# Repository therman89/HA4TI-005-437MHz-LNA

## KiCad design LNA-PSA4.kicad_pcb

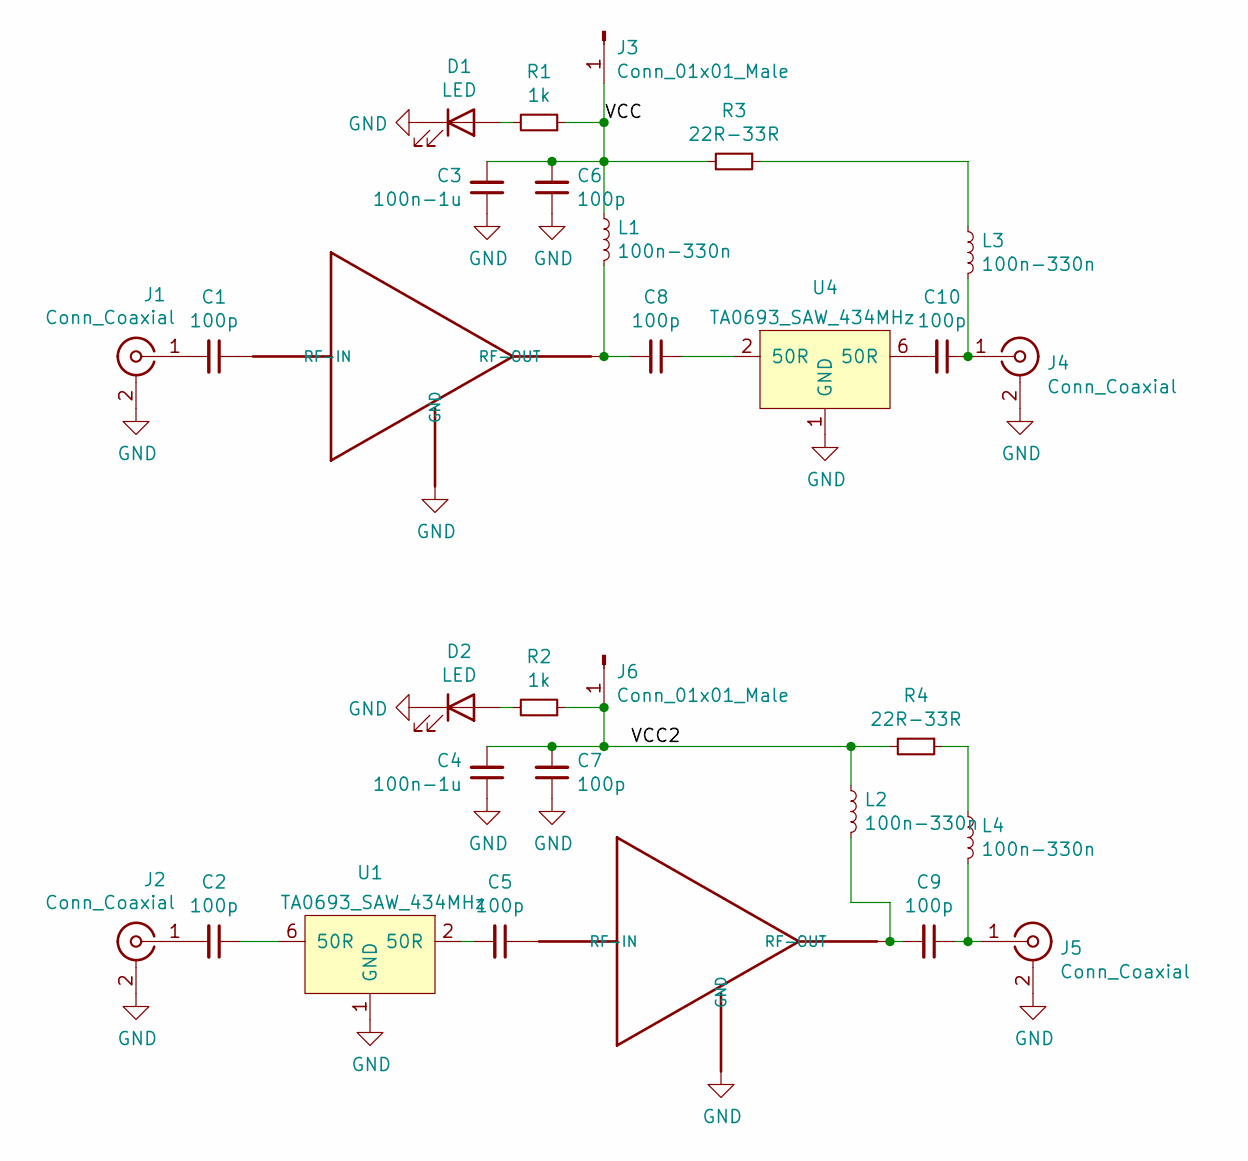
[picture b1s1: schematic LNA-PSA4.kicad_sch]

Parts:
C1, C2, C5, C8, C9, C10: 100p; C_0603_1608Metric
C3, C4: 100n-1u; C_0603_1608Metric_Pad1.05x0.95mm_HandSolder
C6, C7: 100p; C_0603_1608Metric_Pad1.05x0.95mm_HandSolder
D1, D2: LED; LED_0603_1608Metric_Castellated
J1, J2, J4, J5: Conn_Coaxial; SMA_Molex_73251-1153_EdgeMount_Horizontal
J3, J6: Conn_01x01_Male; PinHeader_1x01_P2.54mm_Vertical
L1, L2, L3, L4: 100n-330n; L_0603_1608Metric
R1, R2: 1k; R_0603_1608Metric_Pad1.05x0.95mm_HandSolder
R3, R4: 22R-33R; R_0603_1608Metric_Pad1.05x0.95mm_HandSolder
U1, U4: TA0693_SAW_434MHz; TA0693A_SAW_437MHz
U2, U3: PSA4-5043+

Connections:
/VCC: C3.2, C6.2, J3.1, L1.1, R1.1, R3.2
/VCC2: C4.2, C7.2, J6.1, L2.1, R2.1, R4.2
GND: C3.1, C4.1, C6.1, C7.1, D1.1 (K), D2.1 (K), J1.2 (Ext), J2.2 (Ext), J4.2 (Ext), J5.2 (Ext), U1.1 (GND), U1.3 (GND), U1.4 (GND), U1.5 (GND), U1.7 (GND), U1.8 (GND), U2.2 (GND), U2.4 (GND), U3.2 (GND), U3.4 (GND), U4.1 (GND), U4.3 (GND), U4.4 (GND), U4.5 (GND), U4.7 (GND), U4.8 (GND)
unnamed: C1.1, U2.3 (RF-IN)
unnamed: C1.2, J1.1 (In)
unnamed: C2.1, U1.6 (50R)
unnamed: C2.2, J2.1 (In)
unnamed: C5.1, U3.3 (RF-IN)
unnamed: C5.2, U1.2 (50R)
unnamed: C8.1, U4.2 (50R)
unnamed: C8.2, L1.2, U2.1 (RF-OUT)
unnamed: C9.1, J5.1 (In), L4.2
unnamed: C9.2, L2.2, U3.1 (RF-OUT)
unnamed: C10.1, J4.1 (In), L3.2
unnamed: C10.2, U4.6 (50R)
unnamed: D1.2 (A), R1.2
unnamed: D2.2 (A), R2.2
unnamed: L3.1, R3.1
unnamed: L4.1, R4.1

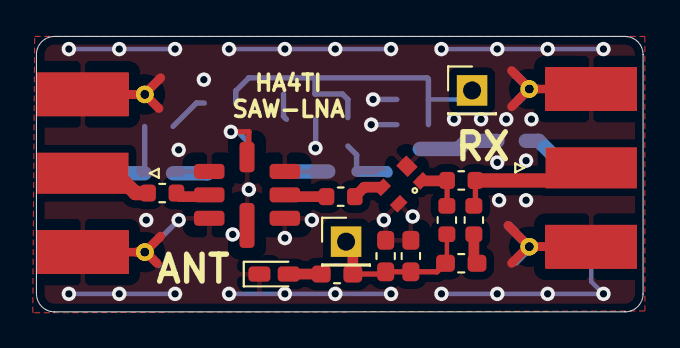
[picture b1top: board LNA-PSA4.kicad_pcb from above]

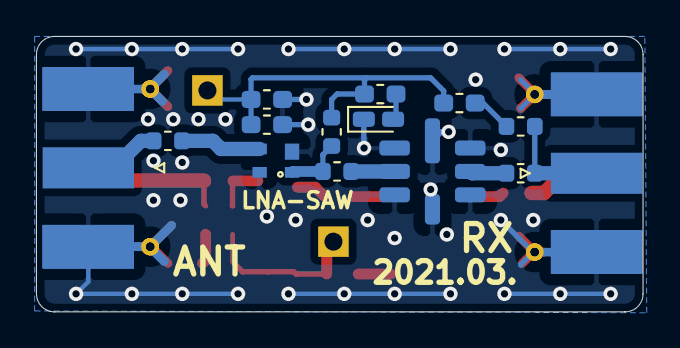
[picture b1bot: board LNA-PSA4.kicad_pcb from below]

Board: 2 copper layers, 33.7 x 15.3 mm, 30 parts (14 on the bottom side), 19 nets.
